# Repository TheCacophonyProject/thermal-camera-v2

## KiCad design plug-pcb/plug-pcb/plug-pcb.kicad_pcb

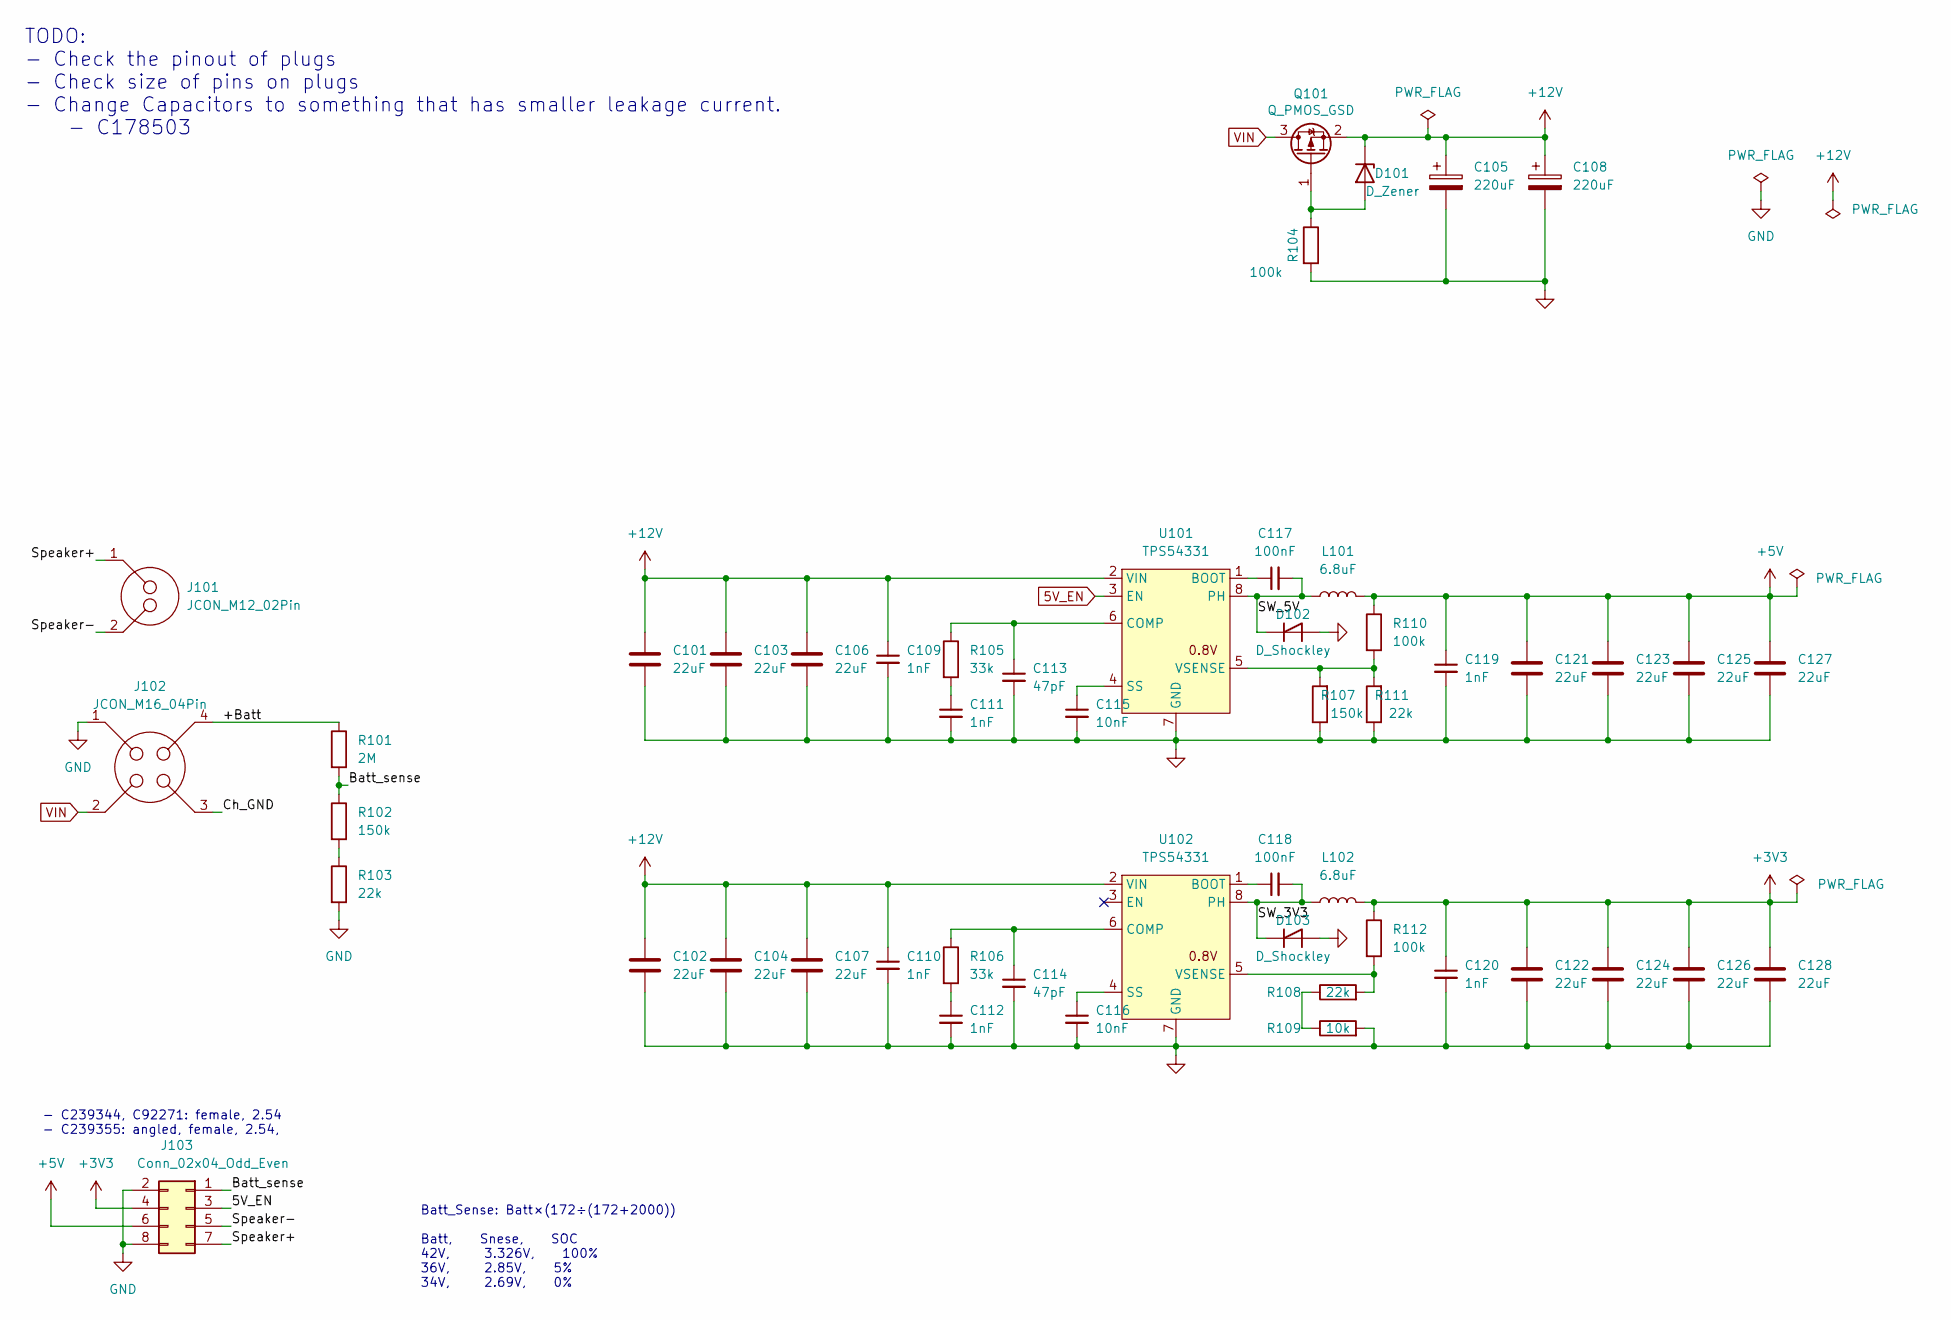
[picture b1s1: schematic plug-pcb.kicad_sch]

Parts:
C101, C102, C103, C104, C106, C107: 22uF; C_0805_2012Metric; LCSC C602037
C105, C108: 220uF; CP_Elec_8x10; LCSC C2895286
C109, C110, C111, C112, C119, C120: 1nF; C_0402_1005Metric; LCSC C1523
C113, C114: 47pF; C_0402_1005Metric; LCSC C1567
C115, C116: 10nF; C_0402_1005Metric; LCSC C15195
C117, C118: 100nF; C_0402_1005Metric; LCSC C307331
C121, C122, C123, C124, C125, C126, C127, C128: 22uF; C_0603_1608Metric; LCSC C86295
D101: D_Zener; LL-34_L3.5-W1.5-RD; LCSC C8062
D102, D103: D_Shockley; D_SMA; LCSC C22452
J101: JCON_M12_02Pin; jcon-2pin-m12
J102: JCON_M16_04Pin; jcon-4pin_m16
J103: Conn_02x04_Odd_Even; HDR-TH_8P-P2.54-H-F-R2-C4-S2.54-W10.2; LCSC C239355
L101, L102: 6.8uF; IND-SMD_L8.0-W8.0_1217AS; LCSC C83465
Q101: Q_PMOS_GSD; SOT-23; LCSC C15127
R101: 2M; R_1210_3225Metric; LCSC C304148
R102: 150k; R_0805_2012Metric; LCSC C74850
R103: 22k; R_0805_2012Metric; LCSC C351592
R104, R110, R112: 100k; R_0402_1005Metric; LCSC C25741
R105, R106: 33k; R_0402_1005Metric; LCSC C25779
R107: 150k; R_0402_1005Metric; LCSC C25755
R108, R111: 22k; R_0402_1005Metric; LCSC C25768
R109: 10k; R_0402_1005Metric; LCSC C25744
U101, U102: TPS54331; SO-8_3.9x4.9mm_P1.27mm; LCSC C9865

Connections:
5V_EN: J103.3, U101.3 (EN)
+3V3: C120.1, C122.1, C124.1, C126.1, C128.1, J103.4, L102.2, R112.1
+5V: C119.1, C121.1, C123.1, C125.1, C127.1, J103.6, L101.2, R110.1
+12V: C101.1, C102.1, C103.1, C104.1, C105.1, C106.1, C107.1, C108.1, C109.1, C110.1, D101.1 (K), Q101.2 (S), U101.2 (VIN), U102.2 (VIN)
/+Batt: J102.4, R101.1
/Batt_sense: J103.1, R101.2, R102.1
/Ch_GND: J102.3
/SW_3V3: C118.2, D103.1 (K), L102.1, U102.8 (PH)
/SW_5V: C117.2, D102.1 (K), L101.1, U101.8 (PH)
/Speaker+: J101.1, J103.7
/Speaker-: J101.2, J103.5
GND: C101.2, C102.2, C103.2, C104.2, C105.2, C106.2, C107.2, C108.2, C109.2, C110.2, C111.2, C112.2, C113.2, C114.2, C115.2, C116.2, C119.2, C120.2, C121.2, C122.2, C123.2, C124.2, C125.2, C126.2, C127.2, C128.2, D102.2 (A), D103.2 (A), J102.1, J103.2, J103.8, R103.2, R104.2, R107.1, R109.2, R111.1, U101.7 (GND), U102.7 (GND)
unnamed: C111.1, R105.2
unnamed: C112.1, R106.2
unnamed: C113.1, R105.1, U101.6 (COMP)
unnamed: C114.1, R106.1, U102.6 (COMP)
unnamed: C115.1, U101.4 (SS)
unnamed: C116.1, U102.4 (SS)
unnamed: C117.1, U101.1 (BOOT)
unnamed: C118.1, U102.1 (BOOT)
unnamed: D101.2 (A), Q101.1 (G), R104.1
unnamed: R102.2, R103.1
unnamed: R107.2, R110.2, R111.2, U101.5 (VSENSE)
unnamed: R108.1, R109.1
unnamed: R108.2, R112.2, U102.5 (VSENSE)
VIN: J102.2, Q101.3 (D)

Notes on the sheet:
TODO: - Check the pinout of plugs - Check size of pins on plugs - Change Capacitors to something that has smaller leakage current. - C178503
- C239344, C92271: female, 2.54 - C239355: angled, female, 2.54,
Batt_Sense: Batt×(172÷(172+2000)) Batt, Snese, SOC 42V, 3.326V, 100% 36V, 2.85V, 5% 34V, 2.69V, 0%

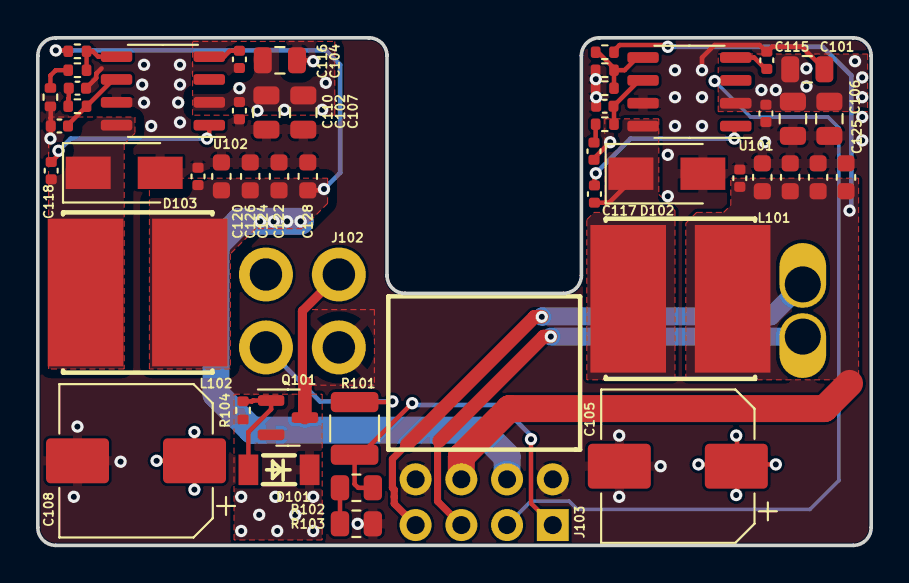
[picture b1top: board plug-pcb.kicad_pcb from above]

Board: 4 copper layers, 46.3 x 28.2 mm, 51 parts (0 on the bottom side), 25 nets.

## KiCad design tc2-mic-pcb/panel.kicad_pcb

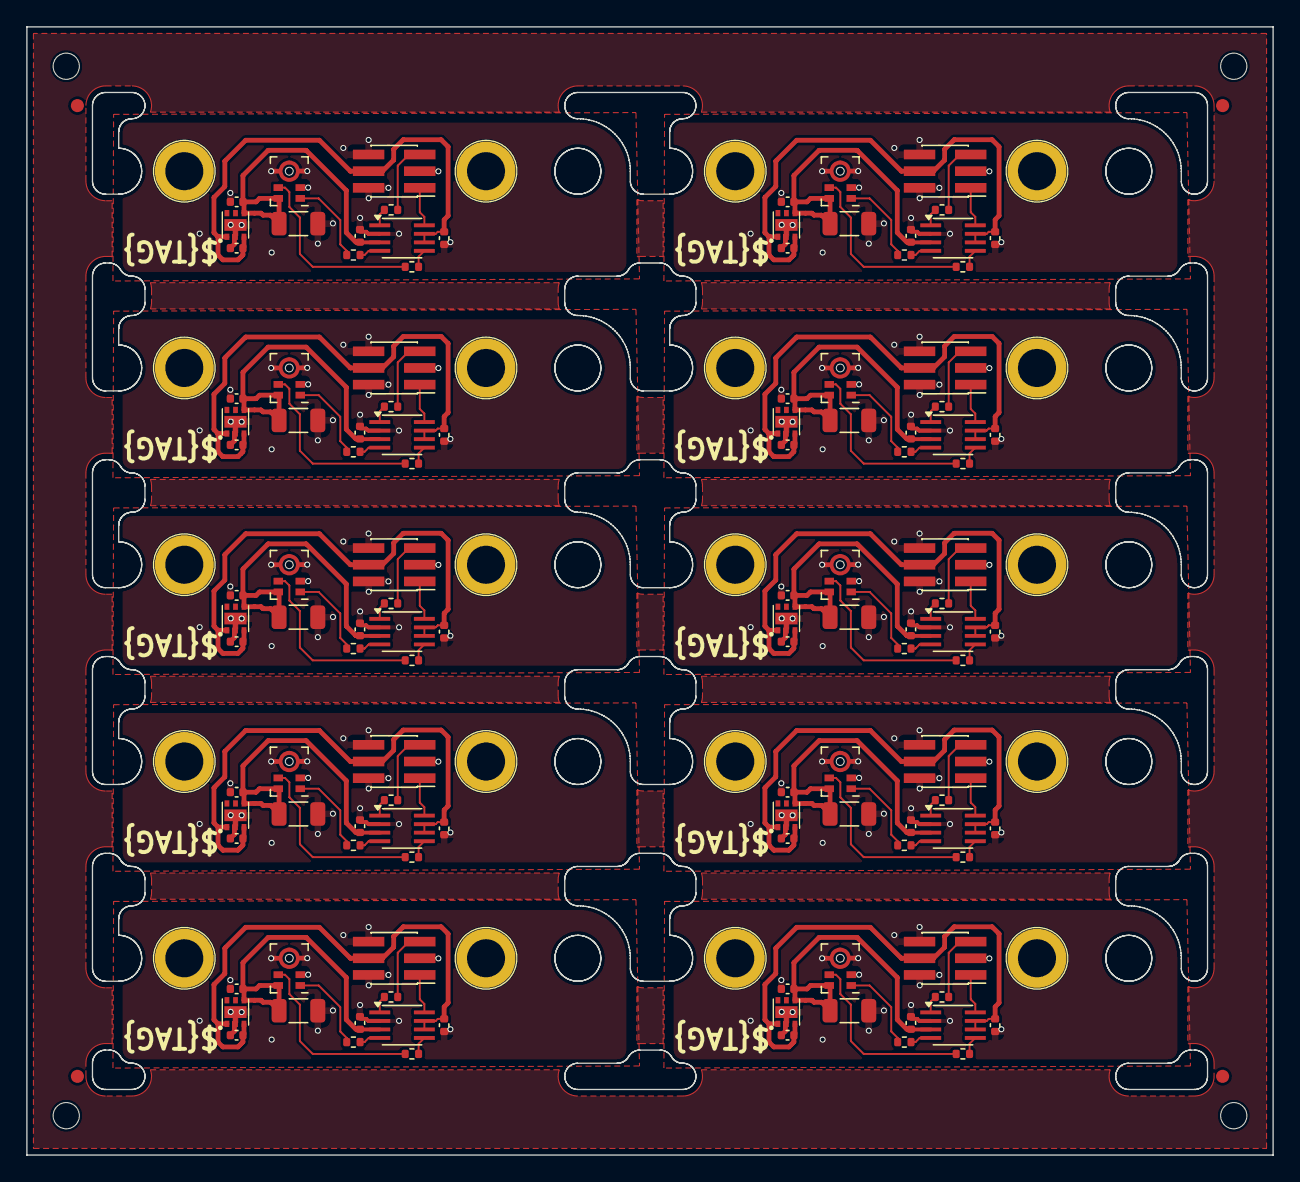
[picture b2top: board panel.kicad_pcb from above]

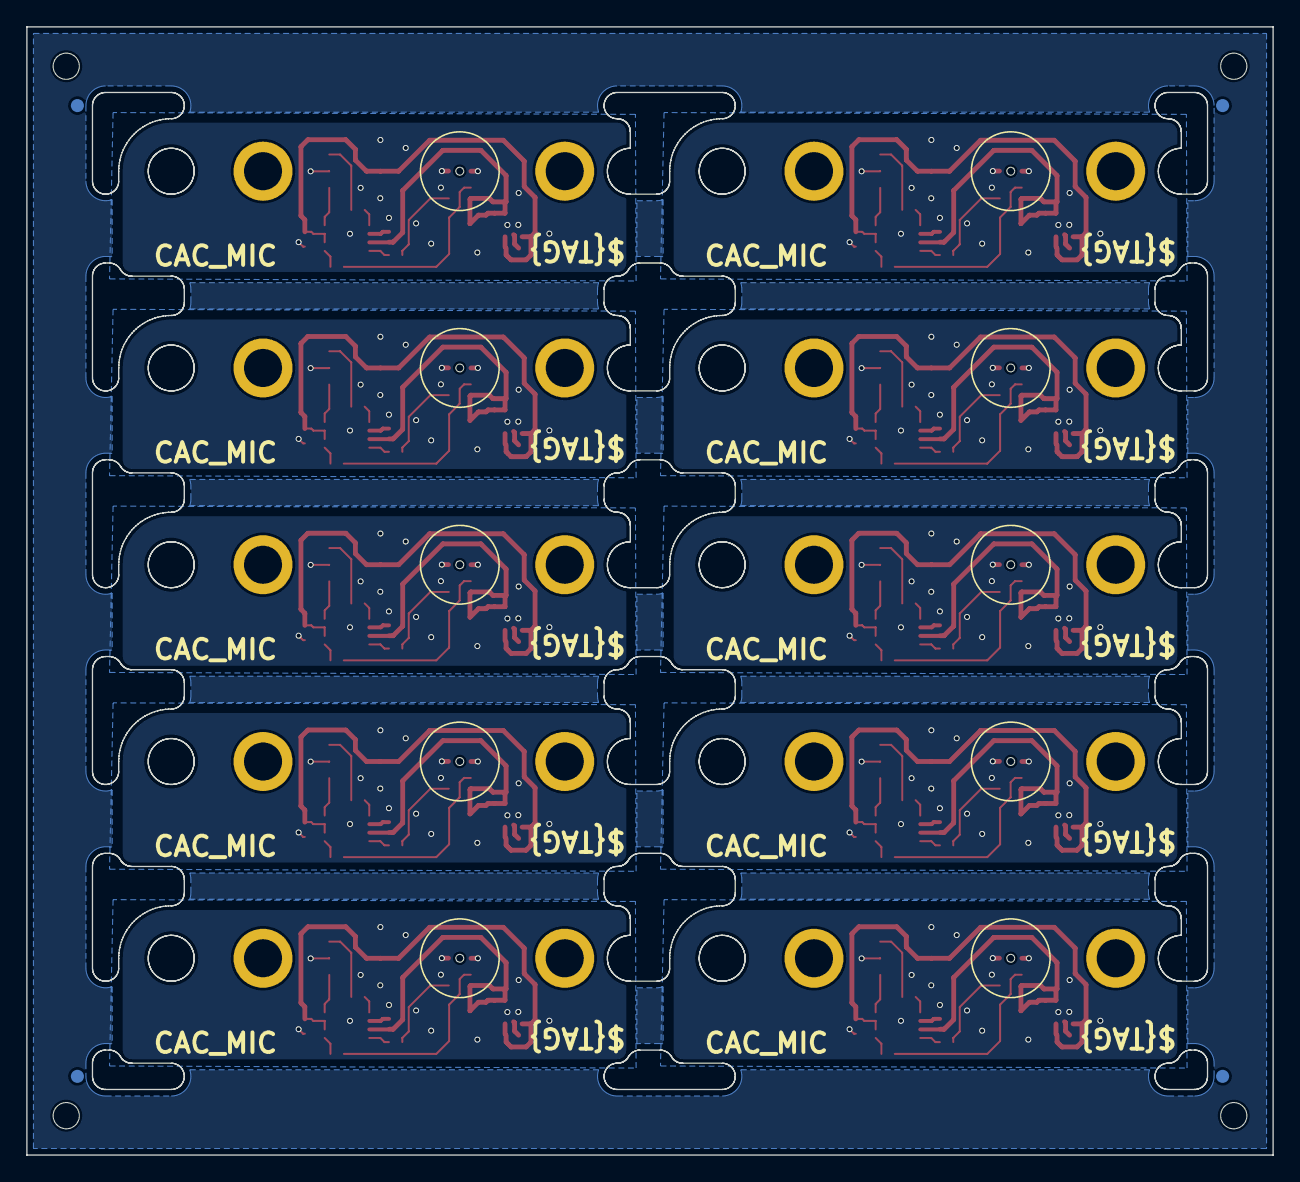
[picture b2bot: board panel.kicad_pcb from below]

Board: 2 copper layers, 95.0 x 86.0 mm, 152 parts (4 on the bottom side), 100 nets.

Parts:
C401-0, C401-1, C401-2, C401-3, C401-4, C401-5, C401-6, C401-7, C401-8, C401-9, C402-0, C402-1, C402-2, C402-3, C402-4, C402-5, C402-6, C402-7, C402-8, C402-9: 100nF; C_0402_1005Metric
C403-0, C403-1, C403-2, C403-3, C403-4, C403-5, C403-6, C403-7, C403-8, C403-9: 100nF; C_1206_3216Metric
C404-0, C404-1, C404-2, C404-3, C404-4, C404-5, C404-6, C404-7, C404-8, C404-9, C405-0, C405-1, C405-2, C405-3, C405-4, C405-5, C405-6, C405-7, C405-8, C405-9: 1uF; C_0402_1005Metric
J401-0, J401-1, J401-2, J401-3, J401-4, J401-5, J401-6, J401-7, J401-8, J401-9: Conn_02x03_Odd_Even; PinHeader_2x03_P1.27mm_Vertical_SMD
J402-0, J402-1, J402-2, J402-3, J402-4, J402-5, J402-6, J402-7, J402-8, J402-9, J403-0, J403-1, J403-2, J403-3, J403-4, J403-5, J403-6, J403-7, J403-8, J403-9: Screw_Terminal_01x01; SMD_BD4.4-L4.4-D2.8
KiKit_FID_B_1, KiKit_FID_B_2, KiKit_FID_B_3, KiKit_FID_B_4: Fiducial
KiKit_FID_T_1, KiKit_FID_T_2, KiKit_FID_T_3, KiKit_FID_T_4: Fiducial
KiKit_TO_1, KiKit_TO_2, KiKit_TO_3, KiKit_TO_4: NPTH
MK401-0, MK401-1, MK401-2, MK401-3, MK401-4, MK401-5, MK401-6, MK401-7, MK401-8, MK401-9: SPH0641LU4H-1; Knowles_LGA-5_3.5x2.65mm_0.6mm_NPTH
R401-0, R401-1, R401-2, R401-3, R401-4, R401-5, R401-6, R401-7, R401-8, R401-9, R402-0, R402-1, R402-2, R402-3, R402-4, R402-5, R402-6, R402-7, R402-8, R402-9, R403-0, R403-1, R403-2, R403-3, R403-4, R403-5, R403-6, R403-7, R403-8, R403-9: 22R; R_0402_1005Metric
U401-0, U401-1, U401-2, U401-3, U401-4, U401-5, U401-6, U401-7, U401-8, U401-9: AP7335-18SNG-7; U-DFN2020-6_L2.0-W2.0-P0.65-BL-EP
U402-0, U402-1, U402-2, U402-3, U402-4, U402-5, U402-6, U402-7, U402-8, U402-9: TXS0102DCT; SSOP-8_2.95x2.8mm_P0.65mm

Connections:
Board_0-+1V8: C401-0.1, C403-0.1, C405-0.1, MK401-0.5 (VDD), U401-0.4 (OUT), U402-0.3 (VCCA)
Board_0-+3V3: C402-0.1, C404-0.1, J401-0.4, U401-0.1 (EN), U401-0.3 (IN), U402-0.6 (OE), U402-0.7 (VCCB)
Board_0-/CLOCK: MK401-0.4 (CLOCK), R401-0.1
Board_0-/CLOCK_PHY: R401-0.2, U402-0.5 (A1)
Board_0-/DATA: R402-0.2, U402-0.4 (A2)
Board_0-/DATA_PHY: MK401-0.1 (DATA), R402-0.1
Board_0-/PDM_DATA_PHY: R403-0.1, U402-0.1 (B2)
Board_0-GND: C401-0.2, C402-0.2, C403-0.2, C404-0.2, C405-0.2, J401-0.2, J401-0.3, J401-0.6, MK401-0.2 (SEL), MK401-0.3 (GND), U401-0.2 (GND), U401-0.7 (GND), U402-0.2 (GND)
Board_0-PDM_CLOCK: J401-0.1, U402-0.8 (B1)
Board_0-PDM_DATA: J401-0.5, R403-0.2
Board_1-+1V8: C401-1.1, C403-1.1, C405-1.1, MK401-1.5 (VDD), U401-1.4 (OUT), U402-1.3 (VCCA)
Board_1-+3V3: C402-1.1, C404-1.1, J401-1.4, U401-1.1 (EN), U401-1.3 (IN), U402-1.6 (OE), U402-1.7 (VCCB)
Board_1-/CLOCK: MK401-1.4 (CLOCK), R401-1.1
Board_1-/CLOCK_PHY: R401-1.2, U402-1.5 (A1)
Board_1-/DATA: R402-1.2, U402-1.4 (A2)
Board_1-/DATA_PHY: MK401-1.1 (DATA), R402-1.1
Board_1-/PDM_DATA_PHY: R403-1.1, U402-1.1 (B2)
Board_1-GND: C401-1.2, C402-1.2, C403-1.2, C404-1.2, C405-1.2, J401-1.2, J401-1.3, J401-1.6, MK401-1.2 (SEL), MK401-1.3 (GND), U401-1.2 (GND), U401-1.7 (GND), U402-1.2 (GND)
Board_1-PDM_CLOCK: J401-1.1, U402-1.8 (B1)
Board_1-PDM_DATA: J401-1.5, R403-1.2
Board_2-+1V8: C401-2.1, C403-2.1, C405-2.1, MK401-2.5 (VDD), U401-2.4 (OUT), U402-2.3 (VCCA)
Board_2-+3V3: C402-2.1, C404-2.1, J401-2.4, U401-2.1 (EN), U401-2.3 (IN), U402-2.6 (OE), U402-2.7 (VCCB)
Board_2-/CLOCK: MK401-2.4 (CLOCK), R401-2.1
Board_2-/CLOCK_PHY: R401-2.2, U402-2.5 (A1)
Board_2-/DATA: R402-2.2, U402-2.4 (A2)
Board_2-/DATA_PHY: MK401-2.1 (DATA), R402-2.1
Board_2-/PDM_DATA_PHY: R403-2.1, U402-2.1 (B2)
Board_2-GND: C401-2.2, C402-2.2, C403-2.2, C404-2.2, C405-2.2, J401-2.2, J401-2.3, J401-2.6, MK401-2.2 (SEL), MK401-2.3 (GND), U401-2.2 (GND), U401-2.7 (GND), U402-2.2 (GND)
Board_2-PDM_CLOCK: J401-2.1, U402-2.8 (B1)
Board_2-PDM_DATA: J401-2.5, R403-2.2
Board_3-+1V8: C401-3.1, C403-3.1, C405-3.1, MK401-3.5 (VDD), U401-3.4 (OUT), U402-3.3 (VCCA)
Board_3-+3V3: C402-3.1, C404-3.1, J401-3.4, U401-3.1 (EN), U401-3.3 (IN), U402-3.6 (OE), U402-3.7 (VCCB)
Board_3-/CLOCK: MK401-3.4 (CLOCK), R401-3.1
Board_3-/CLOCK_PHY: R401-3.2, U402-3.5 (A1)
Board_3-/DATA: R402-3.2, U402-3.4 (A2)
Board_3-/DATA_PHY: MK401-3.1 (DATA), R402-3.1
Board_3-/PDM_DATA_PHY: R403-3.1, U402-3.1 (B2)
Board_3-GND: C401-3.2, C402-3.2, C403-3.2, C404-3.2, C405-3.2, J401-3.2, J401-3.3, J401-3.6, MK401-3.2 (SEL), MK401-3.3 (GND), U401-3.2 (GND), U401-3.7 (GND), U402-3.2 (GND)
Board_3-PDM_CLOCK: J401-3.1, U402-3.8 (B1)
Board_3-PDM_DATA: J401-3.5, R403-3.2
Board_4-+1V8: C401-4.1, C403-4.1, C405-4.1, MK401-4.5 (VDD), U401-4.4 (OUT), U402-4.3 (VCCA)
Board_4-+3V3: C402-4.1, C404-4.1, J401-4.4, U401-4.1 (EN), U401-4.3 (IN), U402-4.6 (OE), U402-4.7 (VCCB)
Board_4-/CLOCK: MK401-4.4 (CLOCK), R401-4.1
Board_4-/CLOCK_PHY: R401-4.2, U402-4.5 (A1)
Board_4-/DATA: R402-4.2, U402-4.4 (A2)
Board_4-/DATA_PHY: MK401-4.1 (DATA), R402-4.1
Board_4-/PDM_DATA_PHY: R403-4.1, U402-4.1 (B2)
Board_4-GND: C401-4.2, C402-4.2, C403-4.2, C404-4.2, C405-4.2, J401-4.2, J401-4.3, J401-4.6, MK401-4.2 (SEL), MK401-4.3 (GND), U401-4.2 (GND), U401-4.7 (GND), U402-4.2 (GND)
Board_4-PDM_CLOCK: J401-4.1, U402-4.8 (B1)
Board_4-PDM_DATA: J401-4.5, R403-4.2
Board_5-+1V8: C401-5.1, C403-5.1, C405-5.1, MK401-5.5 (VDD), U401-5.4 (OUT), U402-5.3 (VCCA)
Board_5-+3V3: C402-5.1, C404-5.1, J401-5.4, U401-5.1 (EN), U401-5.3 (IN), U402-5.6 (OE), U402-5.7 (VCCB)
Board_5-/CLOCK: MK401-5.4 (CLOCK), R401-5.1
Board_5-/CLOCK_PHY: R401-5.2, U402-5.5 (A1)
Board_5-/DATA: R402-5.2, U402-5.4 (A2)
Board_5-/DATA_PHY: MK401-5.1 (DATA), R402-5.1
Board_5-/PDM_DATA_PHY: R403-5.1, U402-5.1 (B2)
Board_5-GND: C401-5.2, C402-5.2, C403-5.2, C404-5.2, C405-5.2, J401-5.2, J401-5.3, J401-5.6, MK401-5.2 (SEL), MK401-5.3 (GND), U401-5.2 (GND), U401-5.7 (GND), U402-5.2 (GND)
Board_5-PDM_CLOCK: J401-5.1, U402-5.8 (B1)
Board_5-PDM_DATA: J401-5.5, R403-5.2
Board_6-+1V8: C401-6.1, C403-6.1, C405-6.1, MK401-6.5 (VDD), U401-6.4 (OUT), U402-6.3 (VCCA)
Board_6-+3V3: C402-6.1, C404-6.1, J401-6.4, U401-6.1 (EN), U401-6.3 (IN), U402-6.6 (OE), U402-6.7 (VCCB)
Board_6-/CLOCK: MK401-6.4 (CLOCK), R401-6.1
Board_6-/CLOCK_PHY: R401-6.2, U402-6.5 (A1)
Board_6-/DATA: R402-6.2, U402-6.4 (A2)
Board_6-/DATA_PHY: MK401-6.1 (DATA), R402-6.1
Board_6-/PDM_DATA_PHY: R403-6.1, U402-6.1 (B2)
Board_6-GND: C401-6.2, C402-6.2, C403-6.2, C404-6.2, C405-6.2, J401-6.2, J401-6.3, J401-6.6, MK401-6.2 (SEL), MK401-6.3 (GND), U401-6.2 (GND), U401-6.7 (GND), U402-6.2 (GND)
Board_6-PDM_CLOCK: J401-6.1, U402-6.8 (B1)
Board_6-PDM_DATA: J401-6.5, R403-6.2
Board_7-+1V8: C401-7.1, C403-7.1, C405-7.1, MK401-7.5 (VDD), U401-7.4 (OUT), U402-7.3 (VCCA)
Board_7-+3V3: C402-7.1, C404-7.1, J401-7.4, U401-7.1 (EN), U401-7.3 (IN), U402-7.6 (OE), U402-7.7 (VCCB)
Board_7-/CLOCK: MK401-7.4 (CLOCK), R401-7.1
Board_7-/CLOCK_PHY: R401-7.2, U402-7.5 (A1)
Board_7-/DATA: R402-7.2, U402-7.4 (A2)
Board_7-/DATA_PHY: MK401-7.1 (DATA), R402-7.1
Board_7-/PDM_DATA_PHY: R403-7.1, U402-7.1 (B2)
Board_7-GND: C401-7.2, C402-7.2, C403-7.2, C404-7.2, C405-7.2, J401-7.2, J401-7.3, J401-7.6, MK401-7.2 (SEL), MK401-7.3 (GND), U401-7.2 (GND), U401-7.7 (GND), U402-7.2 (GND)
Board_7-PDM_CLOCK: J401-7.1, U402-7.8 (B1)
Board_7-PDM_DATA: J401-7.5, R403-7.2
Board_8-+1V8: C401-8.1, C403-8.1, C405-8.1, MK401-8.5 (VDD), U401-8.4 (OUT), U402-8.3 (VCCA)
Board_8-+3V3: C402-8.1, C404-8.1, J401-8.4, U401-8.1 (EN), U401-8.3 (IN), U402-8.6 (OE), U402-8.7 (VCCB)
Board_8-/CLOCK: MK401-8.4 (CLOCK), R401-8.1
Board_8-/CLOCK_PHY: R401-8.2, U402-8.5 (A1)
Board_8-/DATA: R402-8.2, U402-8.4 (A2)
Board_8-/DATA_PHY: MK401-8.1 (DATA), R402-8.1
Board_8-/PDM_DATA_PHY: R403-8.1, U402-8.1 (B2)
Board_8-GND: C401-8.2, C402-8.2, C403-8.2, C404-8.2, C405-8.2, J401-8.2, J401-8.3, J401-8.6, MK401-8.2 (SEL), MK401-8.3 (GND), U401-8.2 (GND), U401-8.7 (GND), U402-8.2 (GND)
Board_8-PDM_CLOCK: J401-8.1, U402-8.8 (B1)
Board_8-PDM_DATA: J401-8.5, R403-8.2
Board_9-+1V8: C401-9.1, C403-9.1, C405-9.1, MK401-9.5 (VDD), U401-9.4 (OUT), U402-9.3 (VCCA)
Board_9-+3V3: C402-9.1, C404-9.1, J401-9.4, U401-9.1 (EN), U401-9.3 (IN), U402-9.6 (OE), U402-9.7 (VCCB)
Board_9-/CLOCK: MK401-9.4 (CLOCK), R401-9.1
Board_9-/CLOCK_PHY: R401-9.2, U402-9.5 (A1)
Board_9-/DATA: R402-9.2, U402-9.4 (A2)
Board_9-/DATA_PHY: MK401-9.1 (DATA), R402-9.1
Board_9-/PDM_DATA_PHY: R403-9.1, U402-9.1 (B2)
Board_9-GND: C401-9.2, C402-9.2, C403-9.2, C404-9.2, C405-9.2, J401-9.2, J401-9.3, J401-9.6, MK401-9.2 (SEL), MK401-9.3 (GND), U401-9.2 (GND), U401-9.7 (GND), U402-9.2 (GND)
Board_9-PDM_CLOCK: J401-9.1, U402-9.8 (B1)
Board_9-PDM_DATA: J401-9.5, R403-9.2

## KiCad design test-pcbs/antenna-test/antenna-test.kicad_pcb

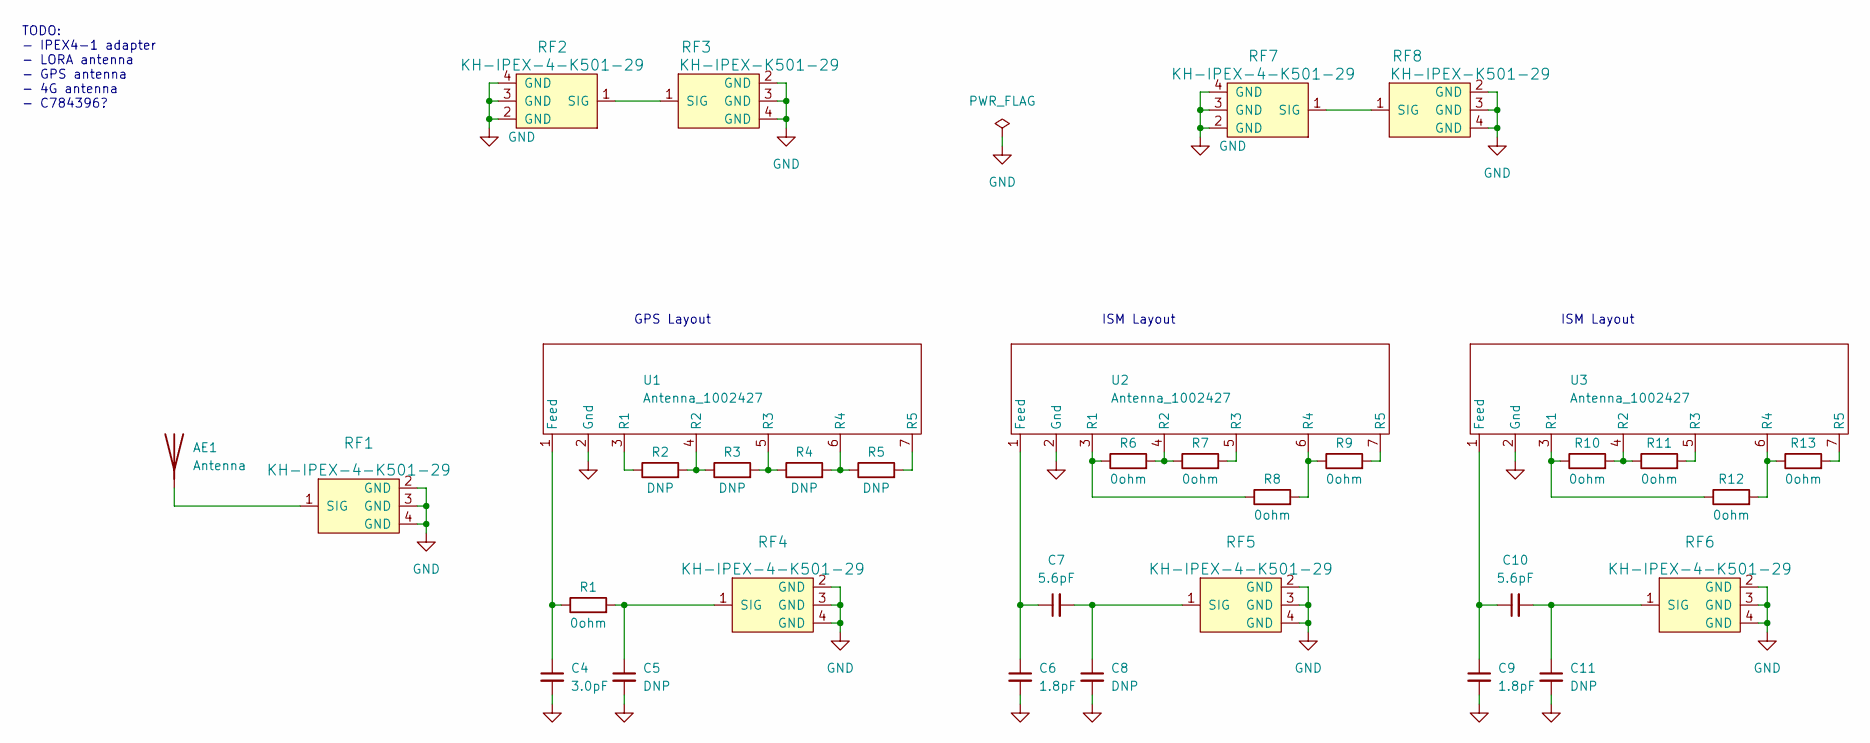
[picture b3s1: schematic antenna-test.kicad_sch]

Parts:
AE1: Antenna; ANT-8_9-PW-LPN
C4: 3.0pF; C_0402_1005Metric; LCSC C318583
C5, C8, C11: DNP; C_0402_1005Metric; LCSC C76903
C6, C9: 1.8pF; C_0402_1005Metric; LCSC C76903
C7, C10: 5.6pF; C_0402_1005Metric; LCSC C384671
R1, R6, R7, R8, R9, R10, R11, R12, R13: 0ohm; R_0402_1005Metric; LCSC C17168
R2, R3, R4, R5: DNP; R_0402_1005Metric
RF1, RF2, RF4, RF5, RF6, RF7: KH-IPEX-4-K501-29; IPEX4-SMD_4P-L1.8-W1.7-LS2.0-L_KH-IPEX4-2020; LCSC C530666
RF3, RF8: KH-IPEX-K501-29; ANT-SMD_KH-IPEX-K501-29; LCSC C411563
U1: Antenna_1002427; ANTENNA_1002427_GPS
U2, U3: Antenna_1002427; ANTENNA_1002427_ISM

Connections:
GND: C4.2, C5.2, C6.2, C8.2, C9.2, C11.2, RF1.2 (GND), RF1.3 (GND), RF1.4 (GND), RF2.2 (GND), RF2.3 (GND), RF2.4 (GND), RF3.2 (GND), RF3.3 (GND), RF3.4 (GND), RF4.2 (GND), RF4.3 (GND), RF4.4 (GND), RF5.2 (GND), RF5.3 (GND), RF5.4 (GND), RF6.2 (GND), RF6.3 (GND), RF6.4 (GND), RF7.2 (GND), RF7.3 (GND), RF7.4 (GND), RF8.2 (GND), RF8.3 (GND), RF8.4 (GND), U1.2 (Gnd), U2.2 (Gnd), U3.2 (Gnd)
unnamed: AE1.1 (A), RF1.1 (SIG)
unnamed: C4.1, R1.1, U1.1 (Feed)
unnamed: C5.1, R1.2, RF4.1 (SIG)
unnamed: C6.1, C7.1, U2.1 (Feed)
unnamed: C7.2, C8.1, RF5.1 (SIG)
unnamed: C9.1, C10.1, U3.1 (Feed)
unnamed: C10.2, C11.1, RF6.1 (SIG)
unnamed: R2.1, U1.3 (R1)
unnamed: R2.2, R3.1, U1.4 (R2)
unnamed: R3.2, R4.1, U1.5 (R3)
unnamed: R4.2, R5.1, U1.6 (R4)
unnamed: R5.2, U1.7 (R5)
unnamed: R6.1, R8.1, U2.3 (R1)
unnamed: R6.2, R7.1, U2.4 (R2)
unnamed: R10.1, R12.1, U3.3 (R1)
unnamed: R10.2, R11.1, U3.4 (R2)
unnamed: R11.2, U3.5 (R3)
unnamed: R12.2, R13.1, U3.6 (R4)
unnamed: R13.2, U3.7 (R5)
unnamed: RF2.1 (SIG), RF3.1 (SIG)
unnamed: RF7.1 (SIG), RF8.1 (SIG)
unnamed: R7.2, U2.5 (R3)
unnamed: R8.2, R9.1, U2.6 (R4)
unnamed: R9.2, U2.7 (R5)

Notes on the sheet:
ISM Layout
GPS Layout
TODO: - IPEX4-1 adapter - LORA antenna - GPS antenna - 4G antenna - C784396?

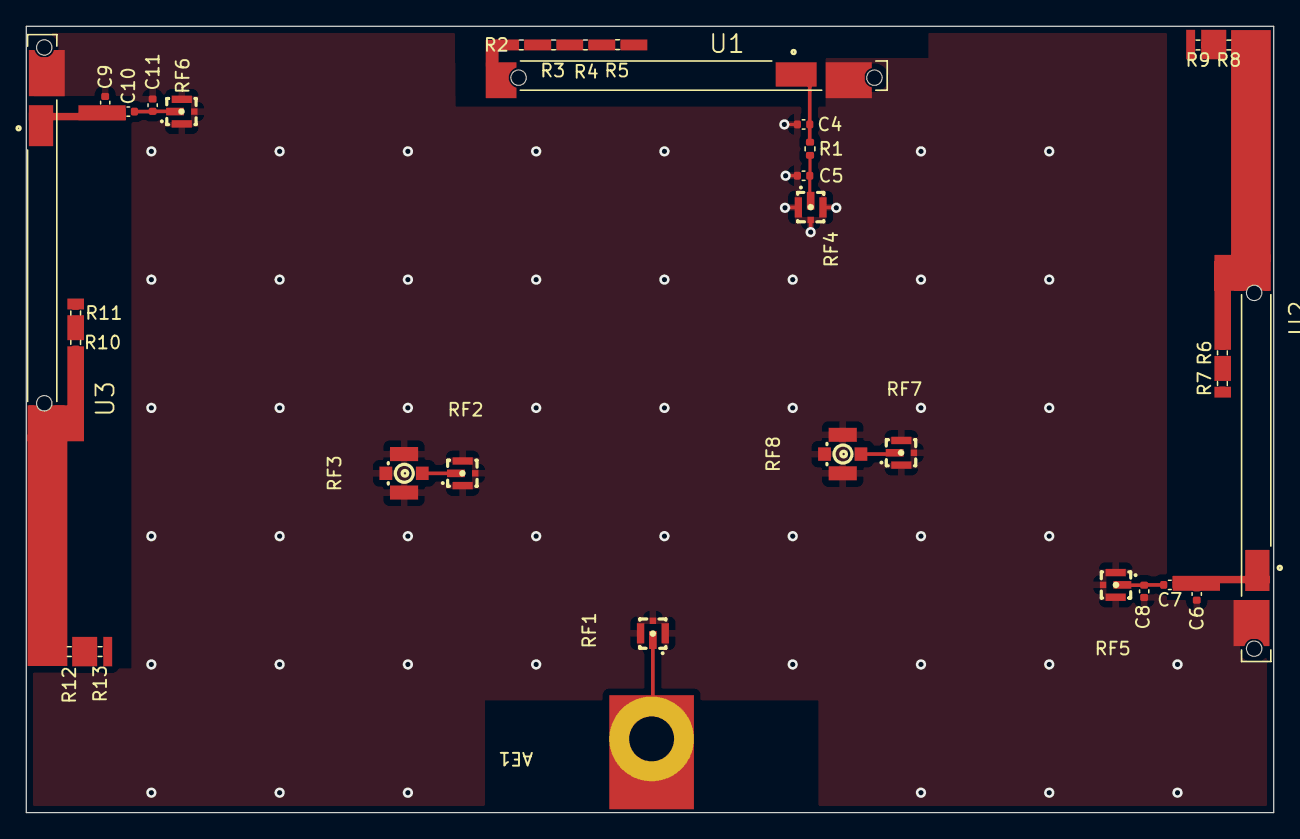
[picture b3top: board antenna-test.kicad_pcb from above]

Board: 4 copper layers, 97.2 x 61.3 mm, 33 parts (0 on the bottom side), 25 nets.

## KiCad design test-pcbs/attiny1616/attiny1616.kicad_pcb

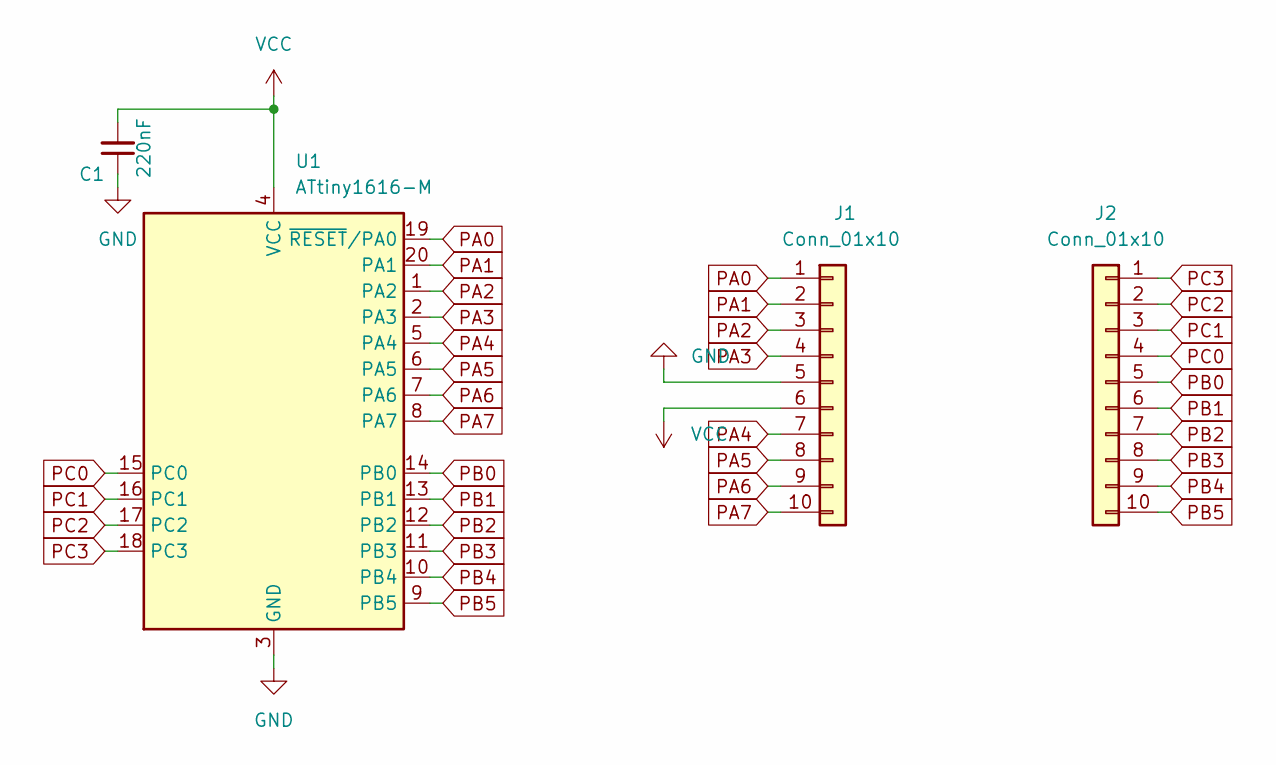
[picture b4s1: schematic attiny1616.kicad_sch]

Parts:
C1: 220nF; C_0402_1005Metric; LCSC C16772
J1, J2: Conn_01x10; PinHeader_1x10_P2.54mm_Vertical
U1: ATtiny1616-M; VQFN-20-1EP_3x3mm_P0.4mm_EP1.7x1.7mm; LCSC C507118

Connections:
GND: C1.1, J1.5, U1.3 (GND), U1.21 (GND)
PA0: J1.1, U1.19 (~RESET/PA0)
PA1: J1.2, U1.20 (PA1)
PA2: J1.3, U1.1 (PA2)
PA3: J1.4, U1.2 (PA3)
PA4: J1.7, U1.5 (PA4)
PA5: J1.8, U1.6 (PA5)
PA6: J1.9, U1.7 (PA6)
PA7: J1.10, U1.8 (PA7)
PB0: J2.5, U1.14 (PB0)
PB1: J2.6, U1.13 (PB1)
PB2: J2.7, U1.12 (PB2)
PB3: J2.8, U1.11 (PB3)
PB4: J2.9, U1.10 (PB4)
PB5: J2.10, U1.9 (PB5)
PC0: J2.4, U1.15 (PC0)
PC1: J2.3, U1.16 (PC1)
PC2: J2.2, U1.17 (PC2)
PC3: J2.1, U1.18 (PC3)
VCC: C1.2, J1.6, U1.4 (VCC)

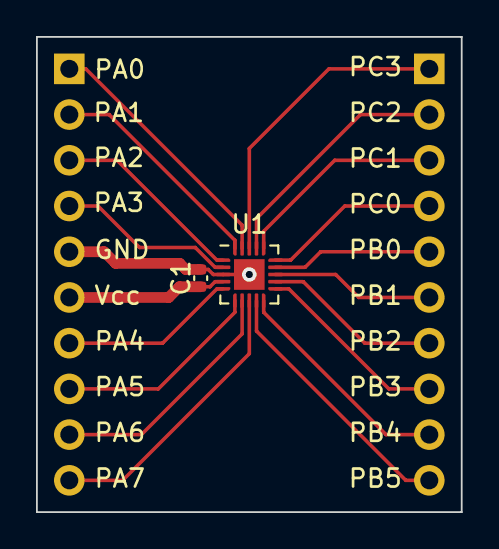
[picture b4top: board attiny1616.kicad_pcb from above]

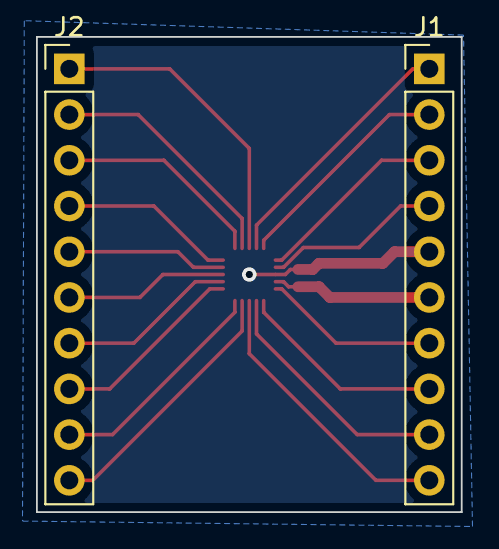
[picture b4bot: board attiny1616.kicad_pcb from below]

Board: 2 copper layers, 23.6 x 26.4 mm, 4 parts (2 on the bottom side), 20 nets.
